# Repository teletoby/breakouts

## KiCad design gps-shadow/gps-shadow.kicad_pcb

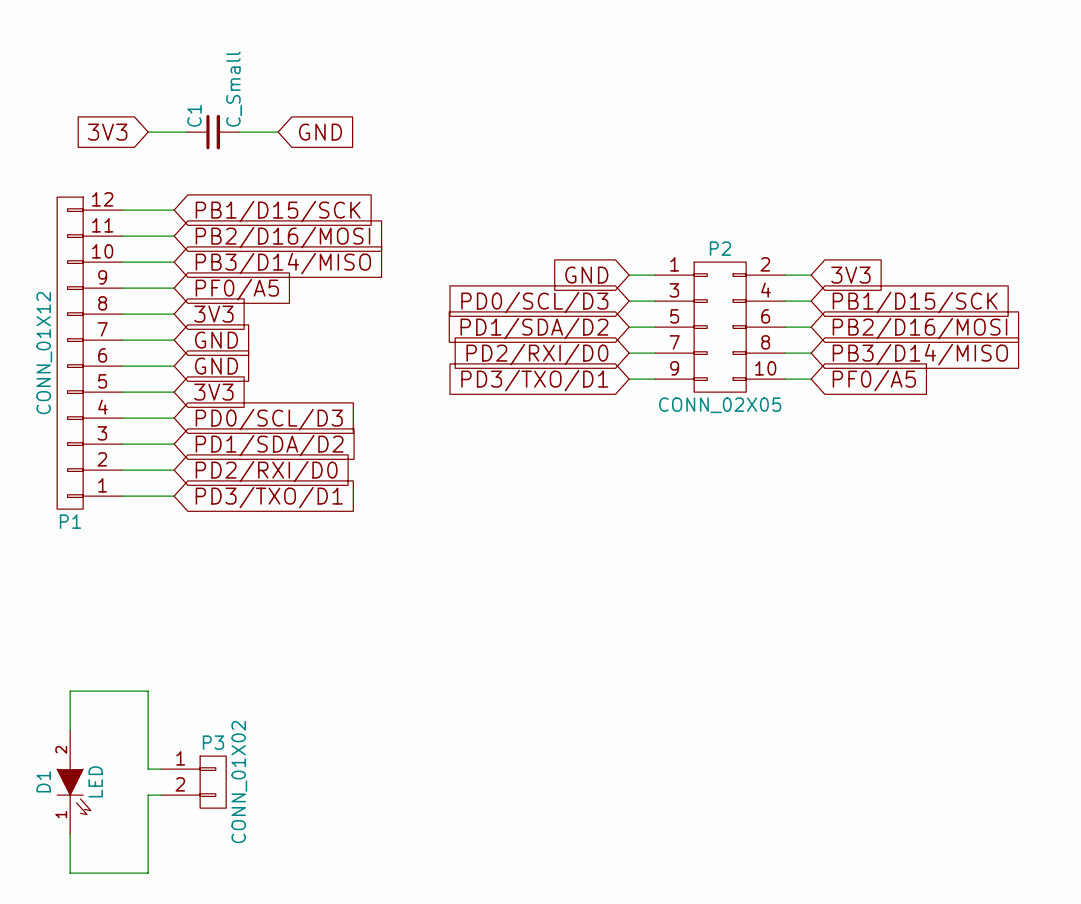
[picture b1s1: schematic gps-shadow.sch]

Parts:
C1: C_Small; C_0805_HandSoldering
D1: LED; LUXEON-3535L
P1: CONN_01X12; FCI-1051922-12
P2: CONN_02X05; Pin_Header_Straight_2x05
P3: CONN_01X02; Pin_Header_Straight_2x01

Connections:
3V3: C1.1, P1.5, P1.8, P2.2
GND: C1.2, P1.6, P1.7, P2.1
unnamed: D1.1 (K), P3.2
unnamed: D1.2 (A), P3.1
PB1/D15/SCK: P1.12, P2.4
PB2/D16/MOSI: P1.11, P2.6
PB3/D14/MISO: P1.10, P2.8
PD0/SCL/D3: P1.4, P2.3
PD1/SDA/D2: P1.3, P2.5
PD2/RXI/D0: P1.2, P2.7
PD3/TXO/D1: P1.1, P2.9
PF0/A5: P1.9, P2.10

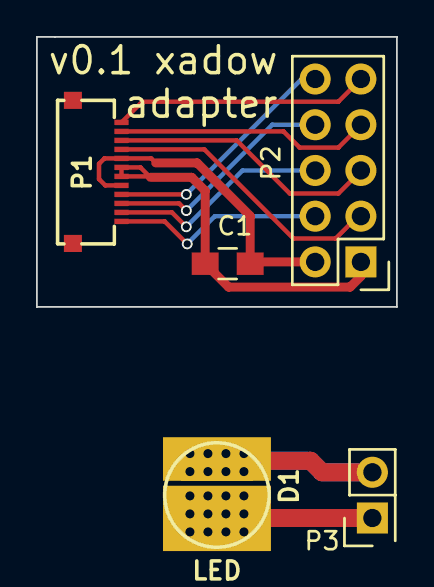
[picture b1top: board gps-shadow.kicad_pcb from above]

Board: 2 copper layers, 20.0 x 15.0 mm, 5 parts (0 on the bottom side), 12 nets.

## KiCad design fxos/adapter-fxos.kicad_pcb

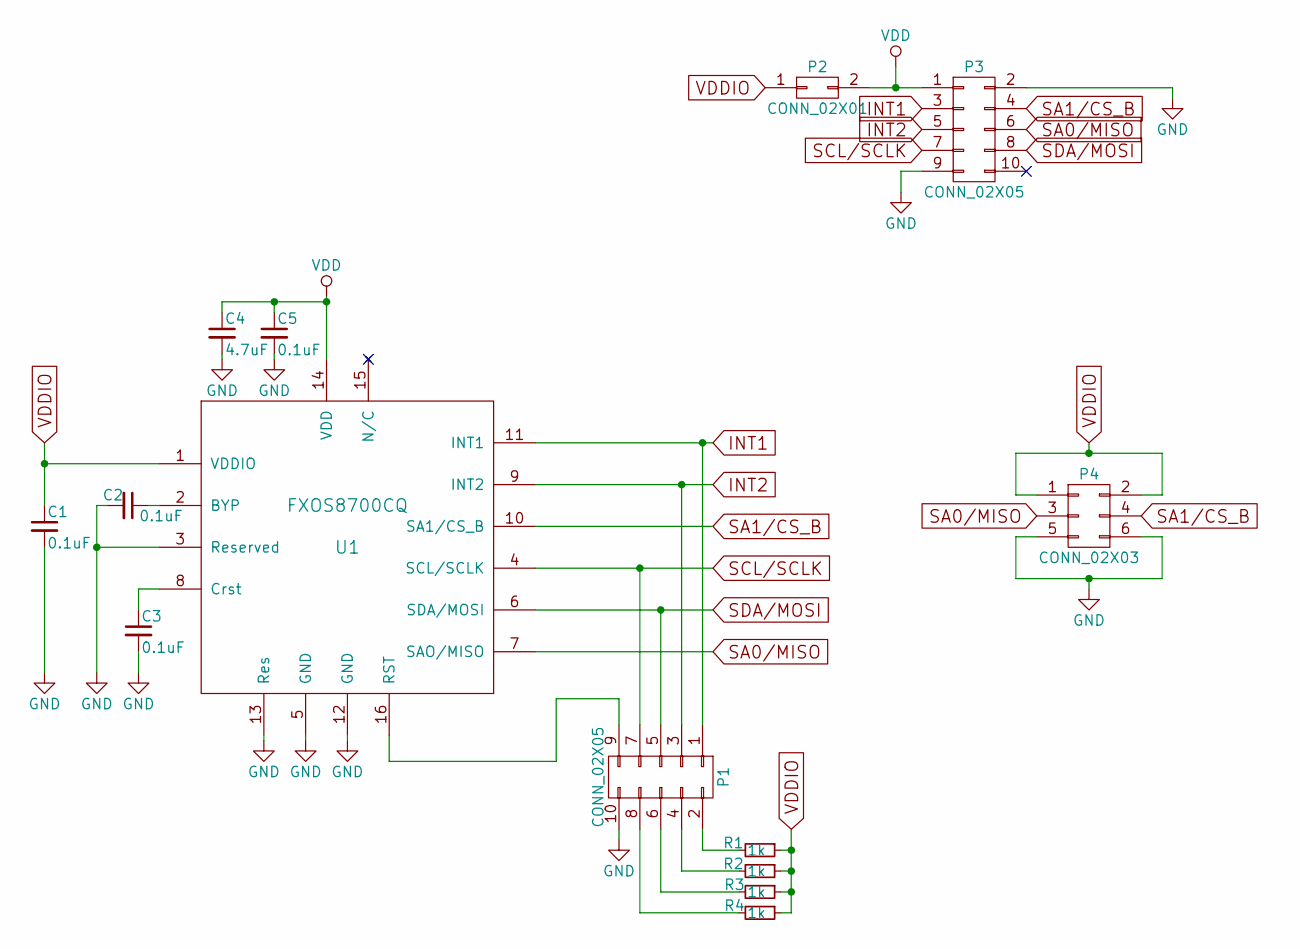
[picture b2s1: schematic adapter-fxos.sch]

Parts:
C1, C2, C3, C5: 0.1uF; C_0805_HandSoldering
C4: 4.7uF; C_0805_HandSoldering
P1, P3: CONN_02X05; Pin_Header_Straight_2x05
P2: CONN_02X01; Pin_Header_Straight_2x01
P4: CONN_02X03; Pin_Header_Straight_2x03
R1, R2, R3, R4: 1k; R_0805_HandSoldering
U1: FXOS8700CQ; QFN-16_3x3mm_p0.5mm-FXOS

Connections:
GND: C1.2, C2.2, C3.2, C4.2, C5.2, P1.10, P3.2, P3.9, P4.5, P4.6, U1.3 (Reserved), U1.5 (GND), U1.12 (GND), U1.13 (Res)
INT1: P1.1, P3.3, U1.11 (INT1)
INT2: P1.3, P3.5, U1.9 (INT2)
unnamed: C2.1, U1.2 (BYP)
unnamed: C3.1, U1.8 (Crst)
unnamed: P1.2, R1.2
unnamed: P1.4, R2.2
unnamed: P1.6, R3.2
unnamed: P1.8, R4.2
unnamed: P1.9, U1.16 (RST)
SA0/MISO: P3.6, P4.3, U1.7 (SAO/MISO)
SA1/CS_B: P3.4, P4.4, U1.10 (SA1/CS_B)
SCL/SCLK: P1.7, P3.7, U1.4 (SCL/SCLK)
SDA/MOSI: P1.5, P3.8, U1.6 (SDA/MOSI)
VDD: C4.1, C5.1, P2.2, P3.1, U1.14 (VDD)
VDDIO: C1.1, P2.1, P4.1, P4.2, R1.1, R2.1, R3.1, R4.1, U1.1 (VDDIO)

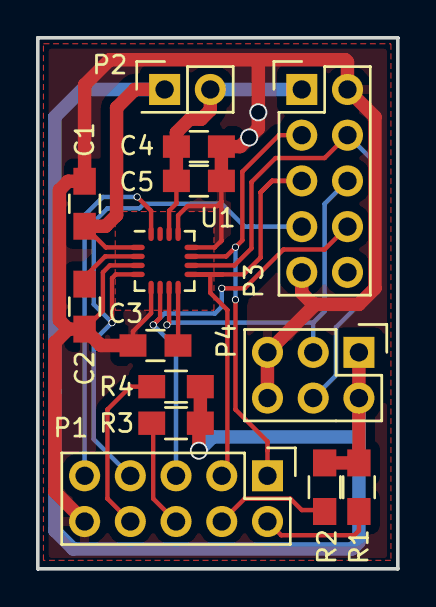
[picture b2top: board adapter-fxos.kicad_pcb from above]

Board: 2 copper layers, 20.0 x 29.5 mm, 14 parts (0 on the bottom side), 16 nets.

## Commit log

2015-12-20 Change paths.
2016-01-03 Solved confusion between fxos breakboard and the one for gps-shadow; generated gerbers for fxos and renamed according to seeed specifications.
